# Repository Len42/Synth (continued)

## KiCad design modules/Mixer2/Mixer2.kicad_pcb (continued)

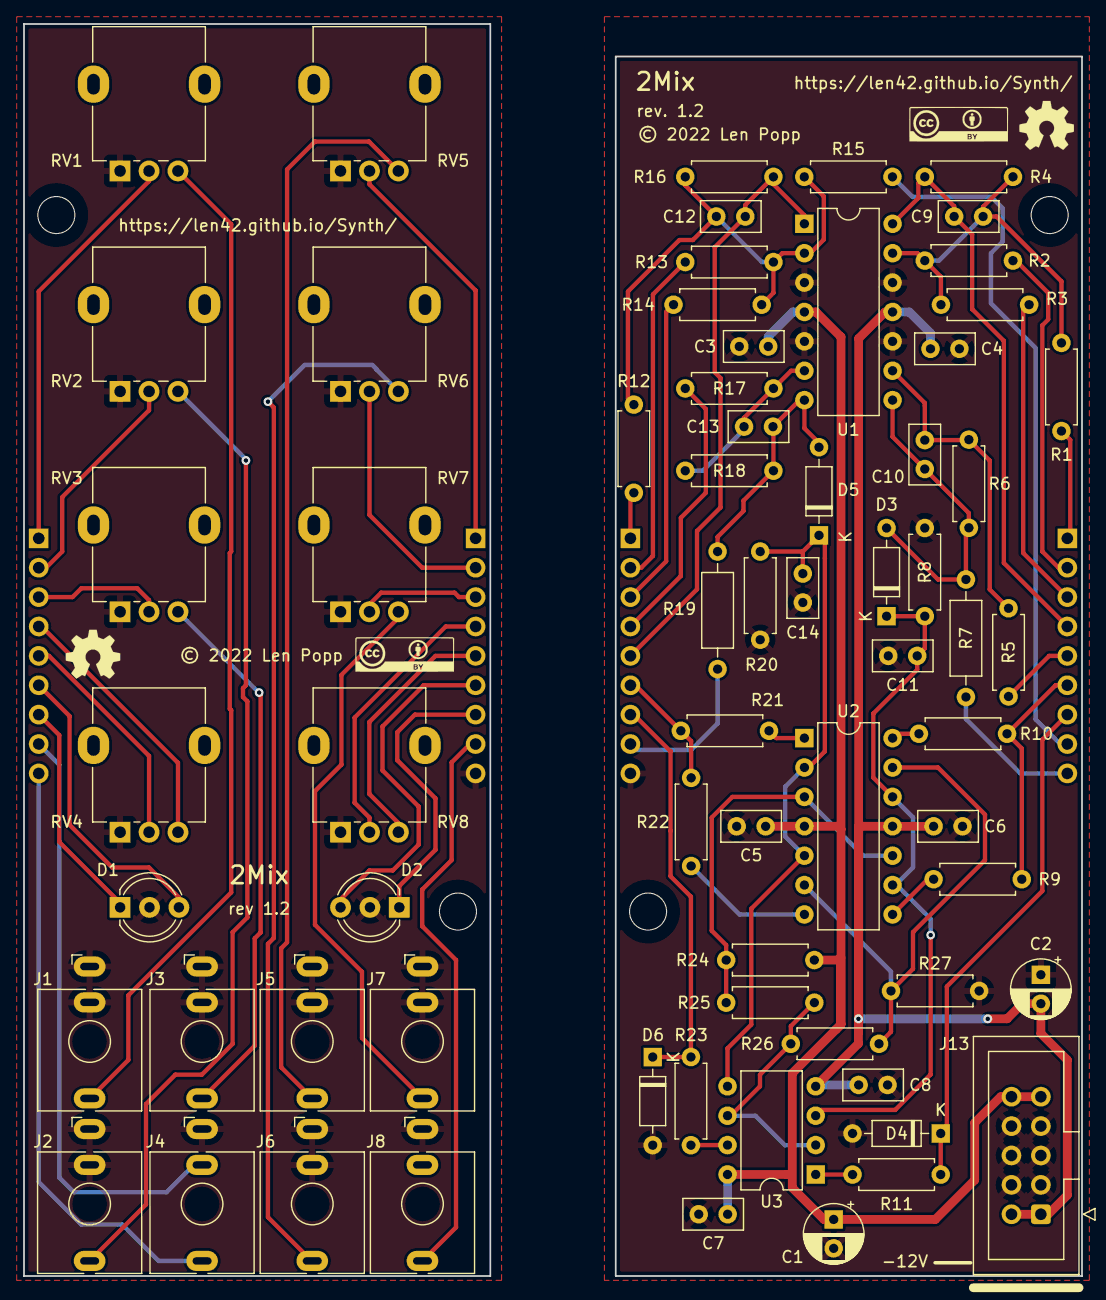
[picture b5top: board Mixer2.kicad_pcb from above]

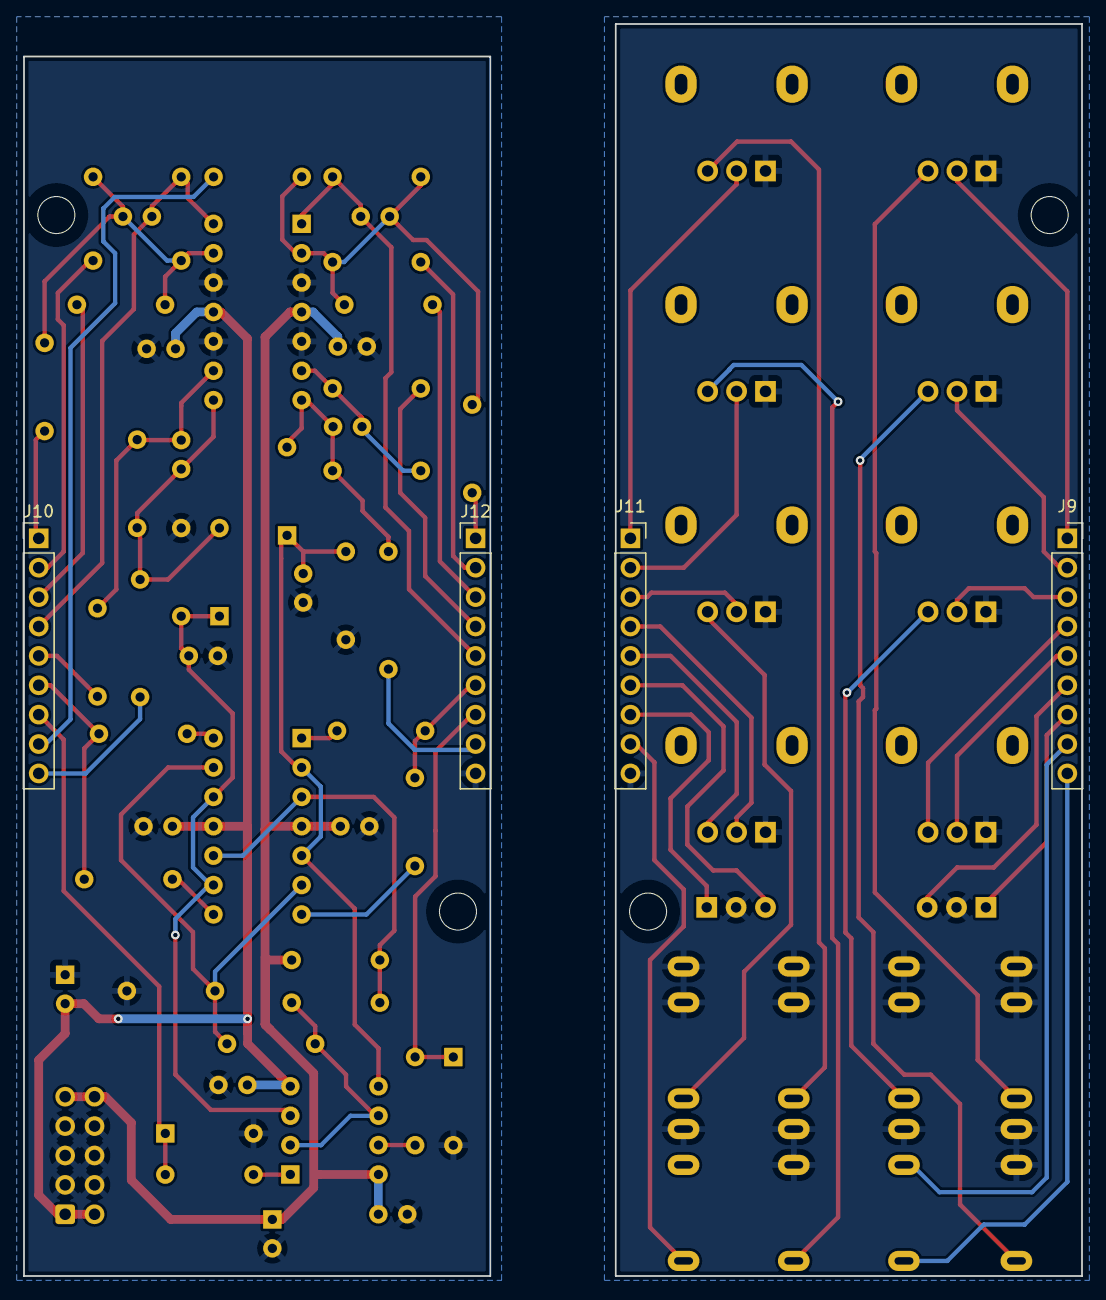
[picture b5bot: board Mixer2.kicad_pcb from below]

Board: 2 copper layers, 91.4 x 108.2 mm, 79 parts (4 on the bottom side), 43 nets.

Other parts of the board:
G1, G2: Logo_CC_BY
G3, G4: Logo_OSHW

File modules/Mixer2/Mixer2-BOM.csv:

Ref,Qty,Value,Value2,Note,Description,Datasheet,Manufacturer,ManuPartNum,Distributor1,DistributorPartNum1,DistributorPartLink1,Distributor2,DistributorPartNum2,DistributorPartLink2,Distributor3,DistributorPartNum3,DistributorPartLink3
"A1","1","Cable_Eurorack_10","","Length as required","Eurorack 16-10 pin power cable","","","","Thonk","","https://www.thonk.co.uk/shop/eurorack-power-cables/","SynthCube","","https://synthcube.com/cart/eurorack-ribbon-power-cables","Modular Addict","","https://modularaddict.com/parts/eurorack-power-cables-1"
"C1 C2","2","10U","","12 V decoupling","Capacitor - Electrolytic - 12 V decoupling","https://www.mouser.ca/datasheet/2/315/ABA0000C1059-947582.pdf","Panasonic","ECE-A1VKS100I","Mouser","667-ECE-A1VKS100I","https://www.mouser.ca/ProductDetail/667-ECE-A1VKS100I","Thonk","Group_Eurorack_DIY_Essential","https://www.thonk.co.uk/shop/eurorack-diy-essentials/","","",""
"C3 C4 C5 C6 C7 C8 C11 C14","8","100N","","IC decoupling","Capacitor - Ceramic - IC decoupling","https://product.tdk.com/system/files/dam/doc/product/capacit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","TDK","FG18X7R1H104KNT06","Mouser","810-FG18X7R1H104KNT6","https://www.mouser.ca/ProductDetail/810-FG18X7R1H104KNT6","","","","","",""
"C9 C10 C12 C13","4","10P","","","Capacitor - Ceramic","https://product.tdk.com/system/files/dam/doc/product/capacit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","TDK","FG18C0G1H100DNT00","Mouser","810-FG18C0G1H100DNT0","https://www.mouser.ca/ProductDetail/810-FG18C0G1H100DNT0","","","","","",""
"D1 D2","2","LED_Dual_5mm_ACA","","","Dual LED, red and green, common cathode on pin 2","https://www.mouser.ca/datasheet/2/216/WP59SURKCGKW-78112.pdf","Kingbright","WP59SURKCGKW","Mouser","604-WP59SURKCGKW","https://www.mouser.ca/ProductDetail/Kingbright/WP59SURKCGKW?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","","","","","",""
"D3 D4 D5 D6","4","1N4148","","","Switching diode, 100V 0.15A, DO-35","https://www.mouser.ca/datasheet/2/308/1N914_D-2309448.pdf","On Semi / Fairchild","1N4148-T50R","Mouser","512-1N4148T50R","https://www.mouser.ca/ProductDetail/?qs=0lQeLiL1qyZS6rosZp7E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","","","","","",""
"H1 H5 H6 H10","4","HW_Screw_M3x0.50x6","","","Machine screw, M3x0.50x6","","","","","","","","","","","",""
"H3 H8","2","HW_Standoff_F-F_11mm_M3x0.50","","","Standoff, 11mm, female-female, M3x0.50","https://www.thonk.co.uk/wp-content/uploads/2018/05/standoff-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","Ettinger","05.03.111","Thonk","Mech_11mm_Standoff_(x10)","https://www.thonk.co.uk/shop/standoffs/","Mouser","710-970110321","https://www.mouser.ca/ProductDetail/Wurth-Elektronik/9701103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","","",""
"J1 J2 J3 J4 J5 J6 J7 J8","8","WQP-PJ398","","","Audio Jack, 2 Poles (Mono / TS), Switched T Pole (Normalling), QingPu / Thonkiconn","http://www.qingpu-electronics.com/en/products/WQP-PJ398SM-362.html","QingPu / Thonk","PJ398SM / WQP518MA","Thonk","PJ398SM","https://www.thonk.co.uk/shop/thonkiconn/","SynthCube","WQP518MA","https://synthcube.com/cart/3-5mm-euro-jacks","Adafruit","4031","https://www.adafruit.com/product/4031"
"J9 J11","2","Conn_PCB_Front","","","Generic connector, single row, 01x09, script generated (kicad-library-utils/schlib/autogen/connector/)","","","","Adafruit","598","https://www.adafruit.com/product/598","Mouser","710-61303211821","https://www.mouser.ca/ProductDetail/Wurth-Elektronik/6130321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","","",""
"J10 J12","2","Conn_PCB_Back","","","Generic connector, single row, 01x09, script generated (kicad-library-utils/schlib/autogen/connector/)","","","","Adafruit","392","https://www.adafruit.com/product/392","Mouser","649-1012937893601BLF","https://www.mouser.ca/ProductDetail/649-1012937893601BLF","","",""
"J13","1","Conn_Eurorack_10","","","Eurorack 10-pin board power connector","https://www.mouser.ca/datasheet/2/445/61201021621-1717731.pdf","Wurth Elektronik","61201021621","Mouser","710-61201021621","https://www.mouser.ca/ProductDetail/Wurth-Elektronik/6120102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","Mouser","523-G821EU210AAL10Y","https://www.mouser.ca/ProductDetail/523-G821EU210AAL10Y","","",""
"R1 R2 R3 R4 R5 R6 R8 R12 R13 R14 R15 R16 R17 R18 R20","15","100K","1%, 1/6 W","","Resistor","https://www.mouser.ca/datasheet/2/447/Yageo_LR_MFR_1-1714151.pdf","YAGEO","MFR-12FTF52-100K","Mouser","603-MFR-12FTF52-100K","https://www.mouser.ca/ProductDetail/YAGEO/MFR-12FTF52-100K?q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","","","","","",""
"R7 R19","2","51R","5%, 1/4 W","Output limiting","Resistor","https://www.mouser.ca/datasheet/2/447/Yageo_LR_MFR_1-1714151.pdf","YAGEO","MFR-25FBF52-51R","Mouser","603-MFR-25FBF52-51R","https://www.mouser.ca/ProductDetail/?qs=oAGoVhmvjhzVx2bdEH1T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","","","","","",""
"R9 R10 R21 R22","4","10K","1%, 1/6 W","","Resistor","https://www.mouser.ca/datasheet/2/447/Yageo_LR_MFR_1-1714151.pdf","YAGEO","MFR-12FTF52-10K","Mouser","603-MFR-12FTF52-10K","https://www.mouser.ca/ProductDetail/YAGEO/MFR-12FTF52-10K?qs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","","","","","",""
"R11 R23","2","4K7","1%, 1/6 W","","Resistor","https://www.mouser.ca/datasheet/2/447/Yageo_LR_MFR_1-1714151.pdf","YAGEO","MFR-12FTF52-4K7","Mouser","603-MFR-12FTF52-4K7","https://www.mouser.ca/ProductDetail/YAGEO/MFR-12FTF52-4K7?qs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","","","","","",""
"R24","1","75K","1%, 1/6 W","","Resistor","https://www.mouser.ca/datasheet/2/447/Yageo_LR_MFR_1-1714151.pdf","YAGEO","MFR-12FTF52-75K","Mouser","603-MFR-12FTF52-75K","https://www.mouser.ca/ProductDetail/YAGEO/MFR-12FTF52-75K?qs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","","","","","",""
"R25","1","11K","1%, 1/6 W","","Resistor","https://www.mouser.ca/datasheet/2/447/Yageo_LR_MFR_1-1714151.pdf","YAGEO","MFR-12FTF52-11K","Mouser","603-MFR-12FTF52-11K","https://www.mouser.ca/ProductDetail/YAGEO/MFR-12FTF52-11K?qs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","","","","","",""
"R26","1","36K","1%, 1/6 W","","Resistor","https://www.mouser.ca/datasheet/2/447/Yageo_LR_MFR_1-1714151.pdf","YAGEO","MFR-12FTF52-36K","Mouser","603-MFR-12FTF52-36K","https://www.mouser.ca/ProductDetail/YAGEO/MFR-12FTF52-36K?qs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","","","","","",""
"R27","1","200R","1%, 1/6 W","","Resistor","https://www.mouser.ca/datasheet/2/447/Yageo_LR_MFR_1-1714151.pdf","YAGEO","MFR-12FTF52-200R","Mouser","603-MFR-12FTF52-200R","https://www.mouser.ca/ProductDetail/603-MFR-12FTF52-200R","","","","","",""
"RV1 RV2 RV3 RV4 RV5 RV6 RV7 RV8","8","100K","LIN","","Potentiometer","https://www.mouser.ca/datasheet/2/13/alpha_taiwan_08192019_R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","Alpha","RD901F-*","Thonk","Group_Pot_Alpha_6.35mm","https://www.thonk.co.uk/shop/alpha-9mm-pots/","Mouser","311-1940F-*","https://www.mouser.ca/c/passive-components/potentiometers-tr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","SynthCube","9MMALPHAPOTMSTR","https://synthcube.com/cart/alpha-9mm-potentiometer-right-ang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"
"U1 U2","2","TL074","","","Quad Low-Noise JFET-Input Operational Amplifiers, DIP-14/SOIC-14","http://www.ti.com/lit/ds/symlink/tl071.pdf","Texas Instruments","TL074BCN","Mouser","595-TL074BCN","https://www.mouser.ca/ProductDetail/?qs=vxEfx8VrU7BHurOY5iQd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","","","","","",""
"U3","1","TL072","","","Dual Low-Noise JFET-Input Operational Amplifiers, DIP-8/SOIC-8","https://www.ti.com/lit/ds/symlink/tl072b.pdf?ts=1628812694194","Texas Instruments","TL072BCP","Mouser","595-TL072BCP","https://www.mouser.ca/ProductDetail/Texas-Instruments/TL072B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","","","","","",""

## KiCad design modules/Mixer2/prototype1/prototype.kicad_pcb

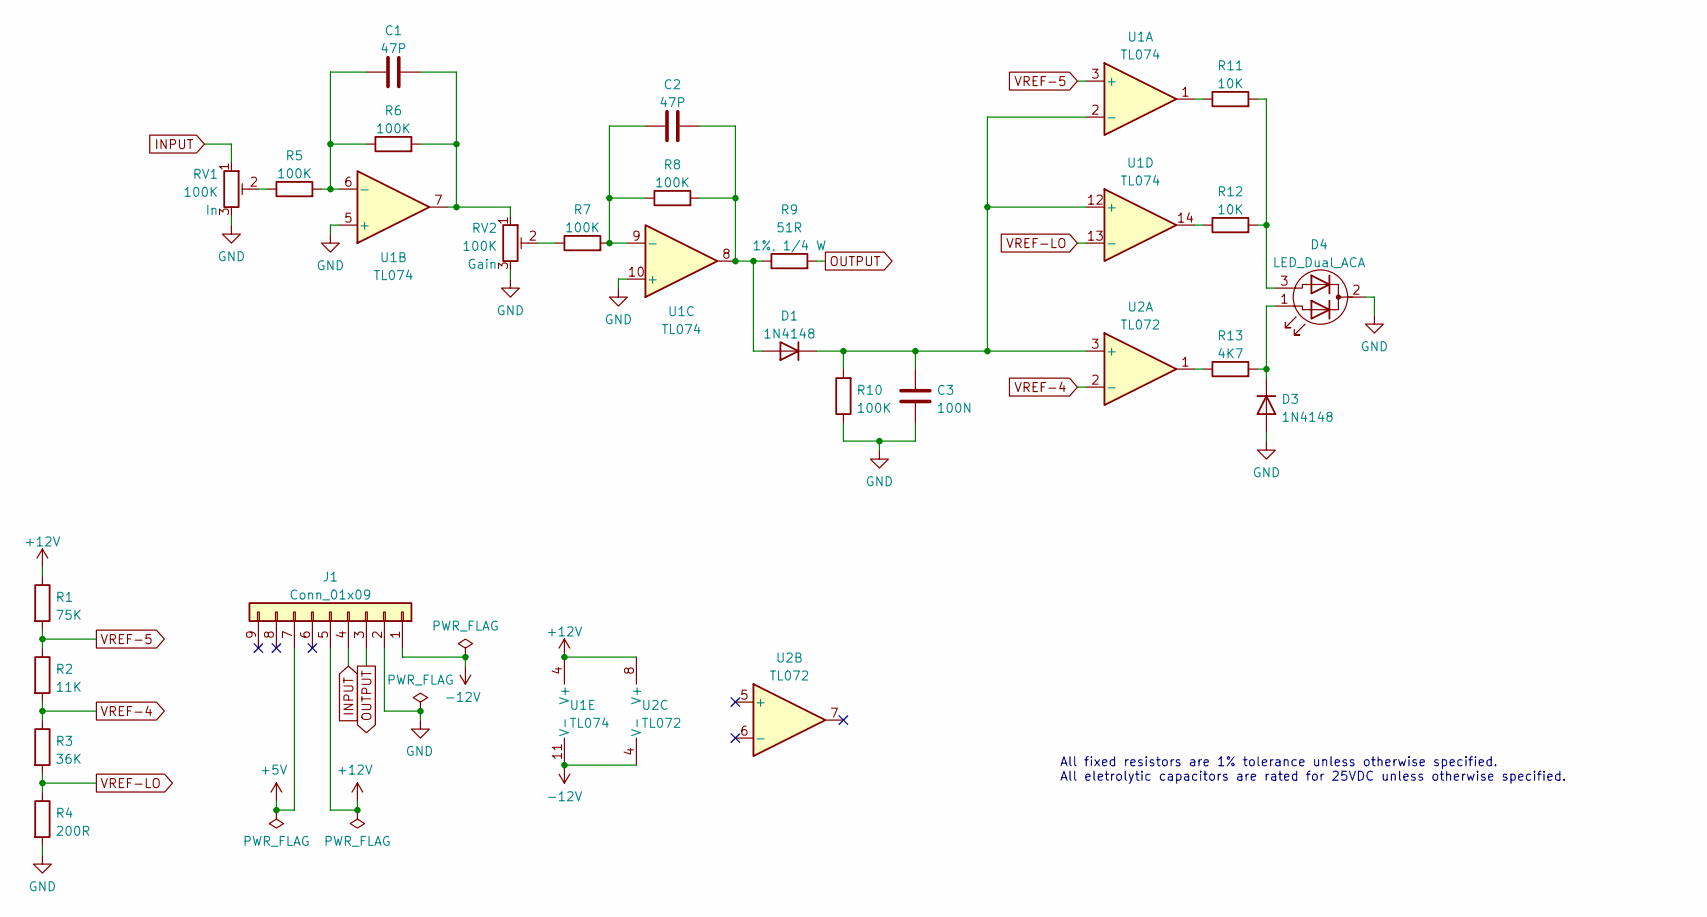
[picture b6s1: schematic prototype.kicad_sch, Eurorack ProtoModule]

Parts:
C1, C2: 47P; C_Disc_D5.0mm_W2.5mm_P2.50mm
C3: 100N; C_Disc_D5.0mm_W2.5mm_P2.50mm; ManufacturerPartNum FG18X7R1H104KNT06
D1: 1N4148; D_DO-35_SOD27_P7.62mm_Horizontal; ManufacturerPartNum 1N4148-T50R
D3: 1N4148; SB_Gen_1; ManufacturerPartNum 1N4148-T50R
D4: LED_Dual_ACA; LED_D5.0mm-3; ManufacturerPartNum WP59SURKCGKW
J1: Conn_01x09; PinHeader_1x09_P2.54mm_Vertical
R1: 75K; SB_Gen_2; ManufacturerPartNum MFR-12*
R2: 11K; R_Axial_DIN0207_L6.3mm_D2.5mm_P7.62mm_Horizontal; ManufacturerPartNum MFR-12*
R3: 36K; R_Axial_DIN0207_L6.3mm_D2.5mm_P7.62mm_Horizontal; ManufacturerPartNum MFR-12*
R4: 200R; SB_Gen_1; ManufacturerPartNum MFR-12*
R5: 100K; SB_Gen_10; ManufacturerPartNum MFR-12*
R6, R8, R10: 100K; SB_Gen_1; ManufacturerPartNum MFR-12*
R7: 100K; R_Axial_DIN0207_L6.3mm_D2.5mm_P7.62mm_Horizontal; ManufacturerPartNum MFR-12*
R9: 51R; SB_Gen_4; ManufacturerPartNum MFR-25FBF52-51R
R11, R12: 10K; R_Axial_DIN0207_L6.3mm_D2.5mm_P7.62mm_Horizontal; ManufacturerPartNum MFR-12*
R13: 4K7; R_Axial_DIN0207_L6.3mm_D2.5mm_P7.62mm_Horizontal; ManufacturerPartNum MFR-12*
RV1, RV2: 100K; Potentiometer_Bourns_3386P_Top; ManufacturerPartNum 3386*
U1: TL074; DIP-14_W7.62mm; ManufacturerPartNum TL074BCN
U2: TL072; DIP-8_W7.62mm; ManufacturerPartNum TL072BCP

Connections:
+5V: J1.7
+12V: J1.5, R1.1, U1.4 (V+), U2.8 (V+)
-12V: J1.1, U1.11 (V-), U2.4 (V-)
GND: C3.2, D3.2 (A), D4.2 (K), J1.2, R4.2, R10.1, RV1.3, RV2.3, U1.5 (+), U1.10 (+)
INPUT: J1.4, RV1.1
unnamed: C1.1, R5.2, R6.1, U1.6 (-)
unnamed: C1.2, R6.2, RV2.1, U1.7
unnamed: C2.1, R7.2, R8.1, U1.9 (-)
unnamed: C2.2, D1.2 (A), R8.2, R9.1, U1.8
unnamed: C3.1, D1.1 (K), R10.2, U1.2 (-), U1.12 (+), U2.3 (+)
unnamed: D3.1 (K), D4.1 (A1), R13.2
unnamed: D4.3 (A2), R11.2, R12.2
unnamed: R5.1, RV1.2
unnamed: R7.1, RV2.2
unnamed: R11.1, U1.1
unnamed: R12.1, U1.14
unnamed: R13.1, U2.1
OUTPUT: J1.3, R9.2
VREF-4: R2.2, R3.1, U2.2 (-)
VREF-5: R1.2, R2.1, U1.3 (+)
VREF-LO: R3.2, R4.1, U1.13 (-)

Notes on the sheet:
All fixed resistors are 1% tolerance unless otherwise specified. All eletrolytic capacitors are rated for 25VDC unless otherwise specified.

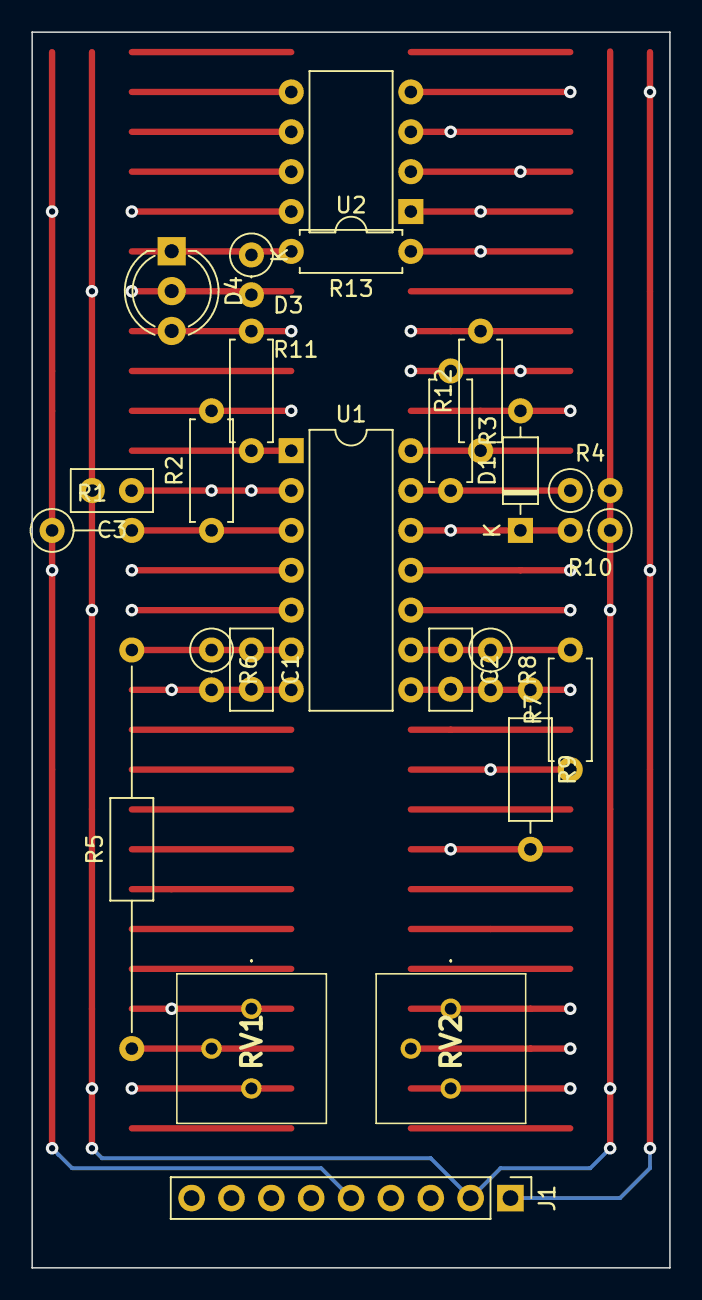
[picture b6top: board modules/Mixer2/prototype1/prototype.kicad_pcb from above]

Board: 6 copper layers, 40.6 x 78.7 mm, 24 parts (0 on the bottom side), 20 nets.
